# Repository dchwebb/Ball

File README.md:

# Ball

Overview
--------

Ball is a Bluetooth remote controller for a Eurorack modular synthesiser. The remote controller is a sphere containing a PCB with an STM32WB35 BLE transmitter connected to an STM MEMS gyroscope. The remote communicates over Bluetooth Low Energy (BLE) with a base unit. The base unit is a standard Eurorack module that converts the three axis gyroscope information into three control voltages.

Remote
------

The remote unit is designed around an STM32WB35 and powered from a Li-Po battery which is charged via a USB micro connection. Battery charging uses a MCP73831 Microchip Charge Management Controller. The battery can be isolated with a slide switch. A mosfet switches either the battery or USB power to a 2.8V linear regulator to power the MCU and gyroscope. A combined voltage divider passes the scaled battery voltage to an ADC in the MCU for battery level monitoring. The voltage divider also controls the inhibit line on the LDO to avoid drawing excessive power from the battery.

The 3-D sensing is carried out on an L3GD20 MEMS gyroscope from STM. This communicates with the MCU via full-duplex SPI. Initial prototyping was carried out using I2C on an Adafruit module and the pins for connecting to the module are fitted to the prototype board. The pins exposing the gyroscope ready and interrupt were bodged into the design via the (now unused) I2C pins. This allows waking from sleep mode via motion detection and readings to be taken from the gyroscope as soon as the ready interrupt fires.

The prototype Remote unit was fitted to a black sphere requisitioned from a child's toy.

[Schematic](https://raw.githubusercontent.com/dchwebb/Ball/main/ball_remote_schematic.pdf)

Base Unit
---------

The base unit also features an STM32WB35. This receives the 3 dimensional gyroscope data from the remote unit over BLE using the HID Joystick specification. (Theoretically this should mean the unit could also support other BLE game controllers but this has not been tested.)

The STM32WB does not contain any DACs so the gyroscope XYZ data is supplied as PWM data which is filtered and scaled to 0-5V. Three LEDs display the current level of each CV output. An additional blue LED showing BLE connection status is positioned behind a PCB Bluetooth 'window' - ie shines through the FR4 with no solder mask or copper.

[Schematic](https://raw.githubusercontent.com/dchwebb/Ball/main/ball_base_schematic.pdf)

Antennas and Matching Network
-----------------------------

The antenna matching network was designed using largely application notes and guesswork. The matching network consists of an 0402 PI network of capacitor/inductor/capacitor connected to an Ignion NN01_102 antenna. Whilst connection strength could probably be improved if matched with a VNA, communications work well in testing.

Power Management and Sleep
--------------------------

As the Remote unit is battery powered various systems are used to reduce power consumption:

When the unit is first powered or reset it begins fast advertising which allows for near-instant connections. After a configurable period has elapsed the unit switches to more infrequent advertising. After a further configurable period of inactivity the unit enters shutdown and can be restarted via the reset button.

Once a connection has been established to the base unit the remote will transmit at full speed (around 380Hz). If no motion is detected after a few seconds the unit will slow down the sampling rate to 190Hz and if no motion is detected after a few more seconds will enter sleep mode. The device can woken via motion (using the gyroscope's interrupt pin), or from the base unit (ie to request a battery level update). If woken from motion the sleep process will repeat once the unit is at rest, or if woken via RF will immediately return to sleep.

The Remote unit's USB peripheral is disabled unless a battery reading of 100% is registered (ie the unit is connected to USB and powered via VBUS). If USB is enabled current draw is around 2mA higher than usual. a USB serial command will also momentarily wake the unit if sleeping.

Measured current consumption of the remote (MCU and all other hardware) is measured as approximately:

- Advertising: 13mA
- Connected: 16mA
- Sleep: 10mA
- Shutdown: 0.4mA

USB Serial Console
------------------

Both the base and remote have USB serial consoles providing a range of diagnostic and configuration information:

Development Software
--------------------

- Schematic and PCB design done in Kicad v6/7.
- Firmware developed in STM32CubeIDE v1.13.2.

Errata
------

Remote:

- SPI MOSI and MISO connections swapped
- Gyroscope Interrupt and Ready pins bodged onto unused I2C pins
- Mosfet Q1 source and drain pins swapped
- Battery charging and monitoring circuit could be improved (eg using a dedicated Battery Management IC such as TI's BQ24079QWRGTRQ1)

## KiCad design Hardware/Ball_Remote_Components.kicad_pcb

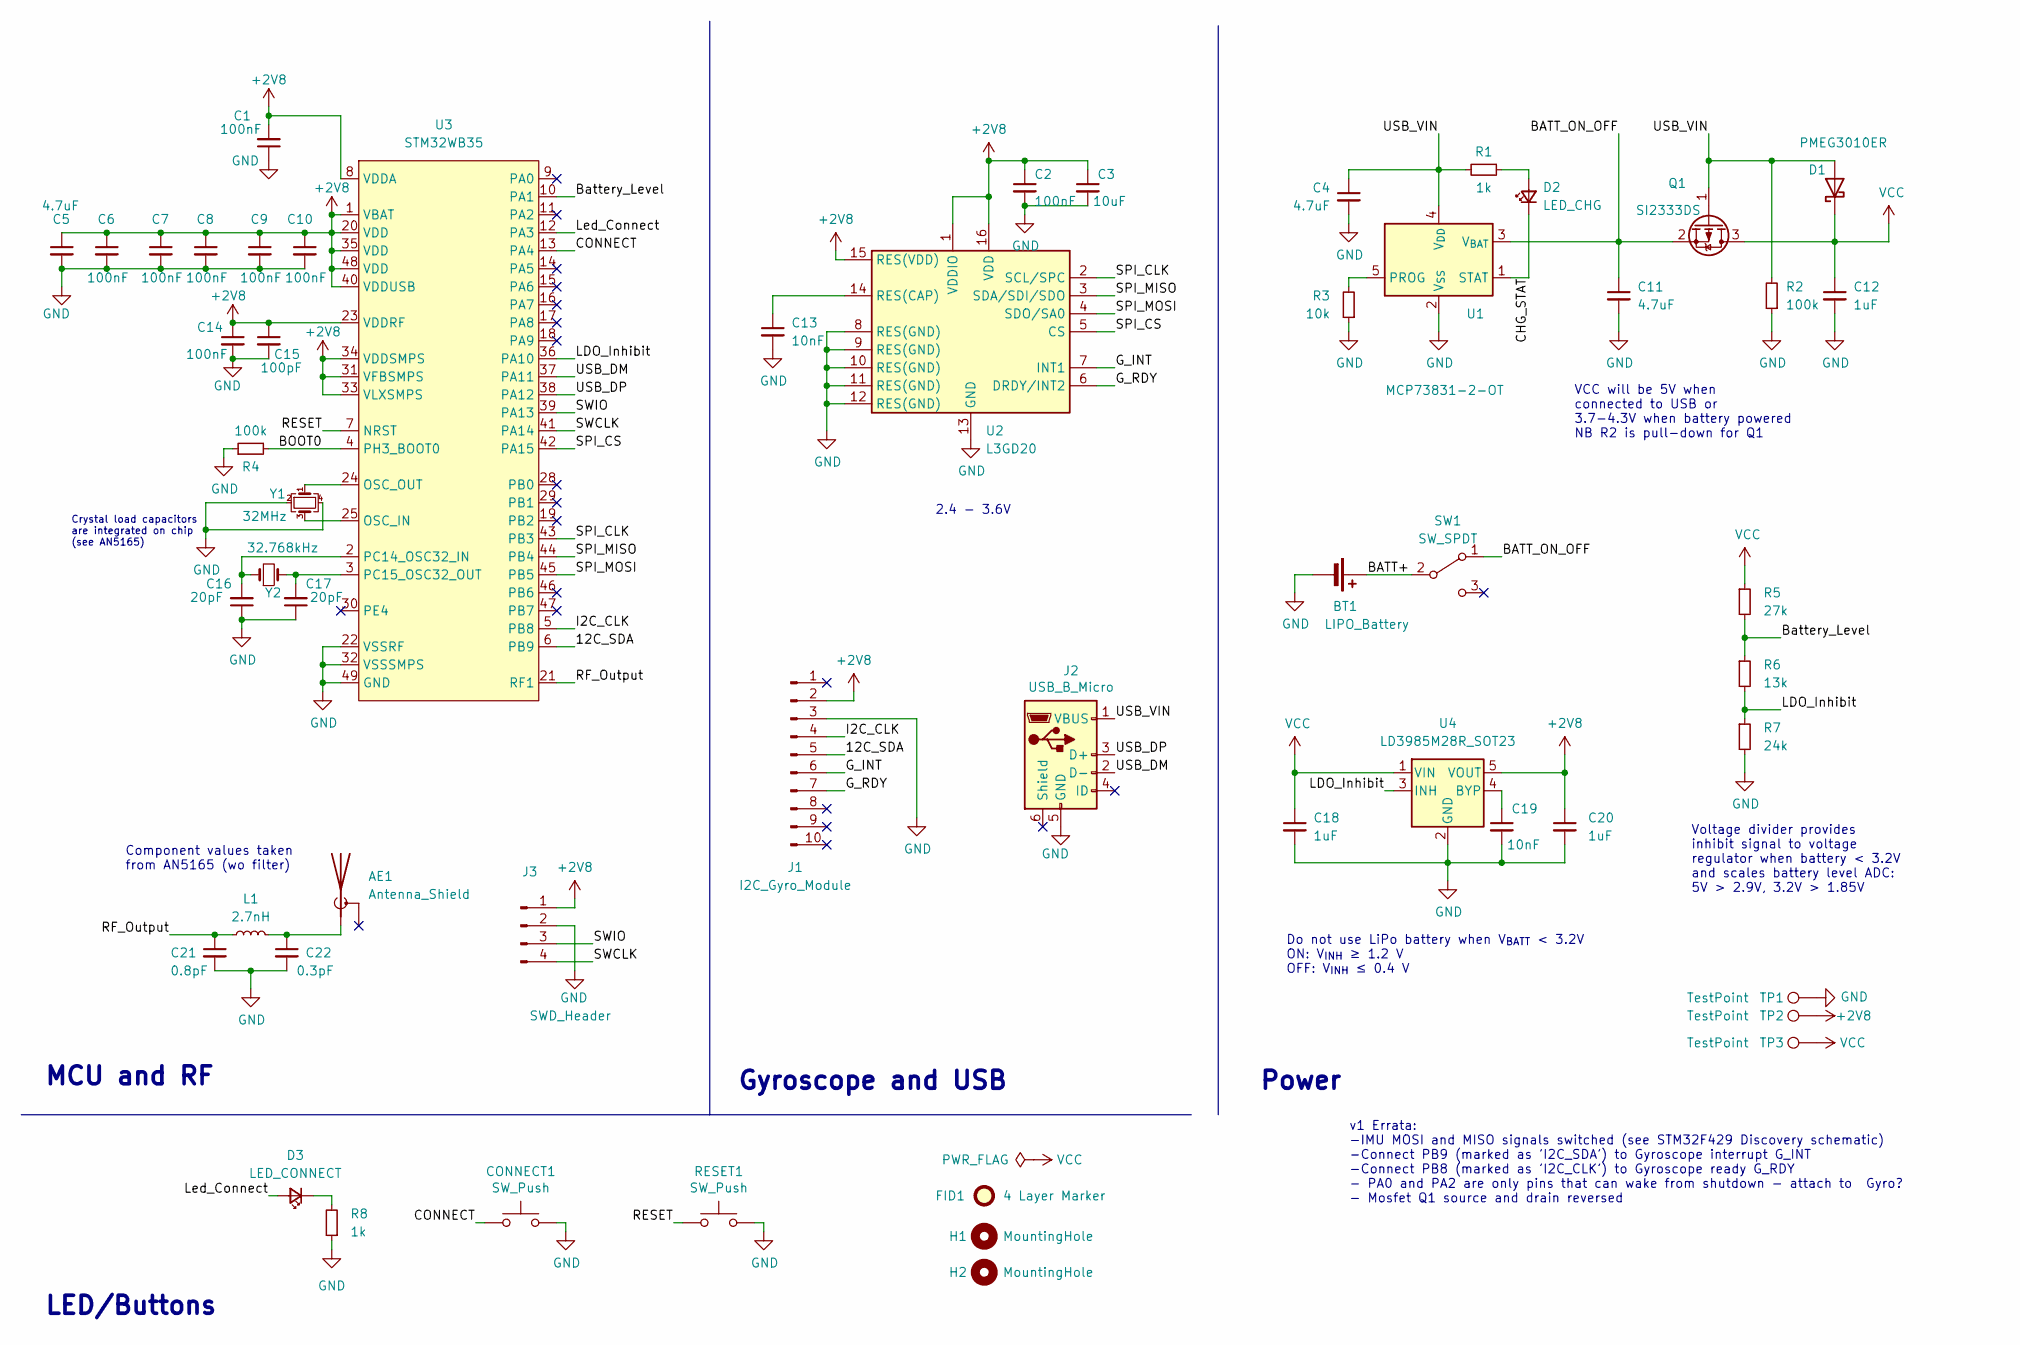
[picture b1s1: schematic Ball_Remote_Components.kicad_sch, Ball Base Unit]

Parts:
AE1: Antenna_Shield; NN01_102
BT1: LIPO_Battery; PinHeader_1x02_P2.54mm_Vertical
C1, C2, C6, C8, C9, C10, C14: 100nF; C_0603_1608Metric
C3: 10uF; C_0603_1608Metric
C4, C5, C11: 4.7uF; C_0603_1608Metric
C7: 100nF; C_0402_1005Metric
C12, C18, C20: 1uF; C_0603_1608Metric
C13, C19: 10nF; C_0603_1608Metric
C15: 100pF; C_0402_1005Metric
C16, C17: 20pF; C_0603_1608Metric
C21: 0.8pF; C_0402_1005Metric
C22: 0.3pF; C_0402_1005Metric
CONNECT1: SW_Push; SW_SPST_EVQQ2
D1: PMEG3010ER; D_SMA
D2: LED_CHG; LED_0603_1608Metric
D3: LED_CONNECT; LED_0603_1608Metric
FID1: 4 Layer Marker; 4_Layer_Markers
H1, H2: MountingHole; MountingHole_3.2mm_M3
J1: I2C_Gyro_Module; PinSocket_1x10_P2.54mm_Vertical
J2: USB_B_Micro; USB_Micro-B_Amphenol
J3: SWD_Header; SWD_header
L1: 2.7nH; L_0402_1005Metric
Q1: SI2333DS; SOT-23
R1: 1k; R_0603_1608Metric; Part_Number C25803
R2, R4: 100k; R_0603_1608Metric; Part_Number C25803
R3: 10k; R_0603_1608Metric; Part_Number C25803
R5: 27k; R_0603_1608Metric; Part_Number C25803
R6: 13k; R_0603_1608Metric; Part_Number C25803
R7: 24k; R_0603_1608Metric; Part_Number C25803
R8: 1k; R_0603_1608Metric
RESET1: SW_Push; SW_Tactile_SPST_Angled_PTS645Vx58-2LFS
SW1: SW_SPDT; SPDT_Slide_Switch
TP1, TP2, TP3: TestPoint; 1.3mm_Test_Point
U1: MCP73831-2-OT; SOT-23-5
U2: L3GD20; LGA-16_4x4mm_P0.65mm_LayoutBorder4x4y
U3: STM32WB35; QFN-48-1EP_7x7mm_P0.5mm_EP5.15x5.15mm_ThermalVias
U4: LD3985M28R_SOT23; SOT-23-5
Y1: 32MHz; Crystal_SMD_Abracon_ABM10-4Pin_2.5x2.0mm
Y2: 32.768kHz; Crystal_SMD_2012-2Pin_2.0x1.2mm

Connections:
+2V8: C1.2, C2.1, C3.1, C5.1, C6.1, C7.1, C8.1, C9.1, C10.1, C14.1, C15.1, C20.1, J1.2, J3.1, TP2.1, U2.1 (VDDIO), U2.15 (RES(VDD)), U2.16 (VDD), U3.1 (VBAT), U3.8 (VDDA), U3.20 (VDD), U3.23 (VDDRF), U3.31 (VFBSMPS), U3.33 (VLXSMPS), U3.34 (VDDSMPS), U3.35 (VDD), U3.40 (VDDUSB), U3.48 (VDD), U4.5 (VOUT)
/12C_SDA: J1.5, U3.6 (PB9)
/BATT+: BT1.1 (+), SW1.2 (B)
/BATT_ON_OFF: C11.1, Q1.2 (S), SW1.1 (A), U1.3 (V_{BAT})
/BOOT0: R4.2, U3.4 (PH3_BOOT0)
/Battery_Level: R5.2, R6.1, U3.10 (PA1)
/CHG_STAT: D2.1 (K), U1.1 (STAT)
/CONNECT: CONNECT1.1, U3.13 (PA4)
/G_INT: J1.6, U2.7 (INT1)
/G_RDY: J1.7, U2.6 (DRDY/INT2)
/I2C_CLK: J1.4, U3.5 (PB8)
/LDO_Inhibit: R6.2, R7.1, U3.36 (PA10), U4.3 (INH)
/Led_Connect: D3.2 (A), U3.12 (PA3)
/RESET: RESET1.1, U3.7 (NRST)
/RF_Output: C21.1, L1.1, U3.21 (RF1)
/SPI_CLK: U2.2 (SCL/SPC), U3.43 (PB3)
/SPI_CS: U2.5 (CS), U3.42 (PA15)
/SPI_MISO: U2.3 (SDA/SDI/SDO), U3.44 (PB4)
/SPI_MOSI: U2.4 (SDO/SA0), U3.45 (PB5)
/SWCLK: J3.4, U3.41 (PA14)
/SWIO: J3.3, U3.39 (PA13)
/USB_DM: J2.2 (D-), U3.37 (PA11)
/USB_DP: J2.3 (D+), U3.38 (PA12)
/USB_VIN: C4.1, D1.2 (A), J2.1 (VBUS), Q1.1 (G), R1.2, R2.2, U1.4 (V_{DD})
GND: BT1.2 (-), C1.1, C2.2, C3.2, C4.2, C5.2, C6.2, C7.2, C8.2, C9.2, C10.2, C11.2, C12.2, C13.2, C14.2, C15.2, C16.1, C17.1, C18.2, C19.2, C20.2, C21.2, C22.2, CONNECT1.2, J1.3, J2.5 (GND), J3.2, R2.1, R3.1, R4.1, R7.2, R8.1, RESET1.2, TP1.1, U1.2 (V_{SS}), U2.8 (RES(GND)), U2.9 (RES(GND)), U2.10 (RES(GND)), U2.11 (RES(GND)), U2.12 (RES(GND)), U2.13 (GND), U3.22 (VSSRF), U3.32 (VSSSMPS), U3.49 (GND), U4.2 (GND), Y1.2, Y1.4
unnamed: AE1.1 (A), C22.1, L1.2
unnamed: D2.2 (A), R1.1
unnamed: D3.1 (K), R8.2
unnamed: R3.2, U1.5 (PROG)
unnamed: C13.1, U2.14 (RES(CAP))
unnamed: U3.25 (OSC_IN), Y1.3
unnamed: U3.24 (OSC_OUT), Y1.1
unnamed: C16.2, U3.2 (PC14_OSC32_IN), Y2.1
unnamed: C17.2, U3.3 (PC15_OSC32_OUT), Y2.2
unnamed: C19.1, U4.4 (BYP)
VCC: C12.1, C18.1, D1.1 (K), Q1.3 (D), R5.1, TP3.1, U4.1 (VIN)

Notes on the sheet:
MCU and RF
Do not use LiPo battery when V_{BATT} < 3.2V ON: V_{INH} ≥ 1.2 V OFF: V_{INH} ≤ 0.4 V
Power
Gyroscope and USB
Component values taken from AN5165 (wo filter)
Voltage divider provides inhibit signal to voltage regulator when battery < 3.2V and scales battery level ADC: 5V > 2.9V, 3.2V > 1.85V
2.4 - 3.6V
LED/Buttons
VCC will be 5V when connected to USB or 3.7-4.3V when battery powered NB R2 is pull-down for Q1
v1 Errata: -IMU MOSI and MISO signals switched (see STM32F429 Discovery schematic) -Connect PB9 (marked as 'I2C_SDA') to Gyroscope interrupt G_INT -Connect PB8 (marked as 'I2C_CLK') to Gyroscope ready G_RDY - PA0 and PA2 are only pins that can wake from shutdown - attach to Gyro? - Mosfet Q1 source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
Crystal load capacitors are integrated on chip (see AN5165)

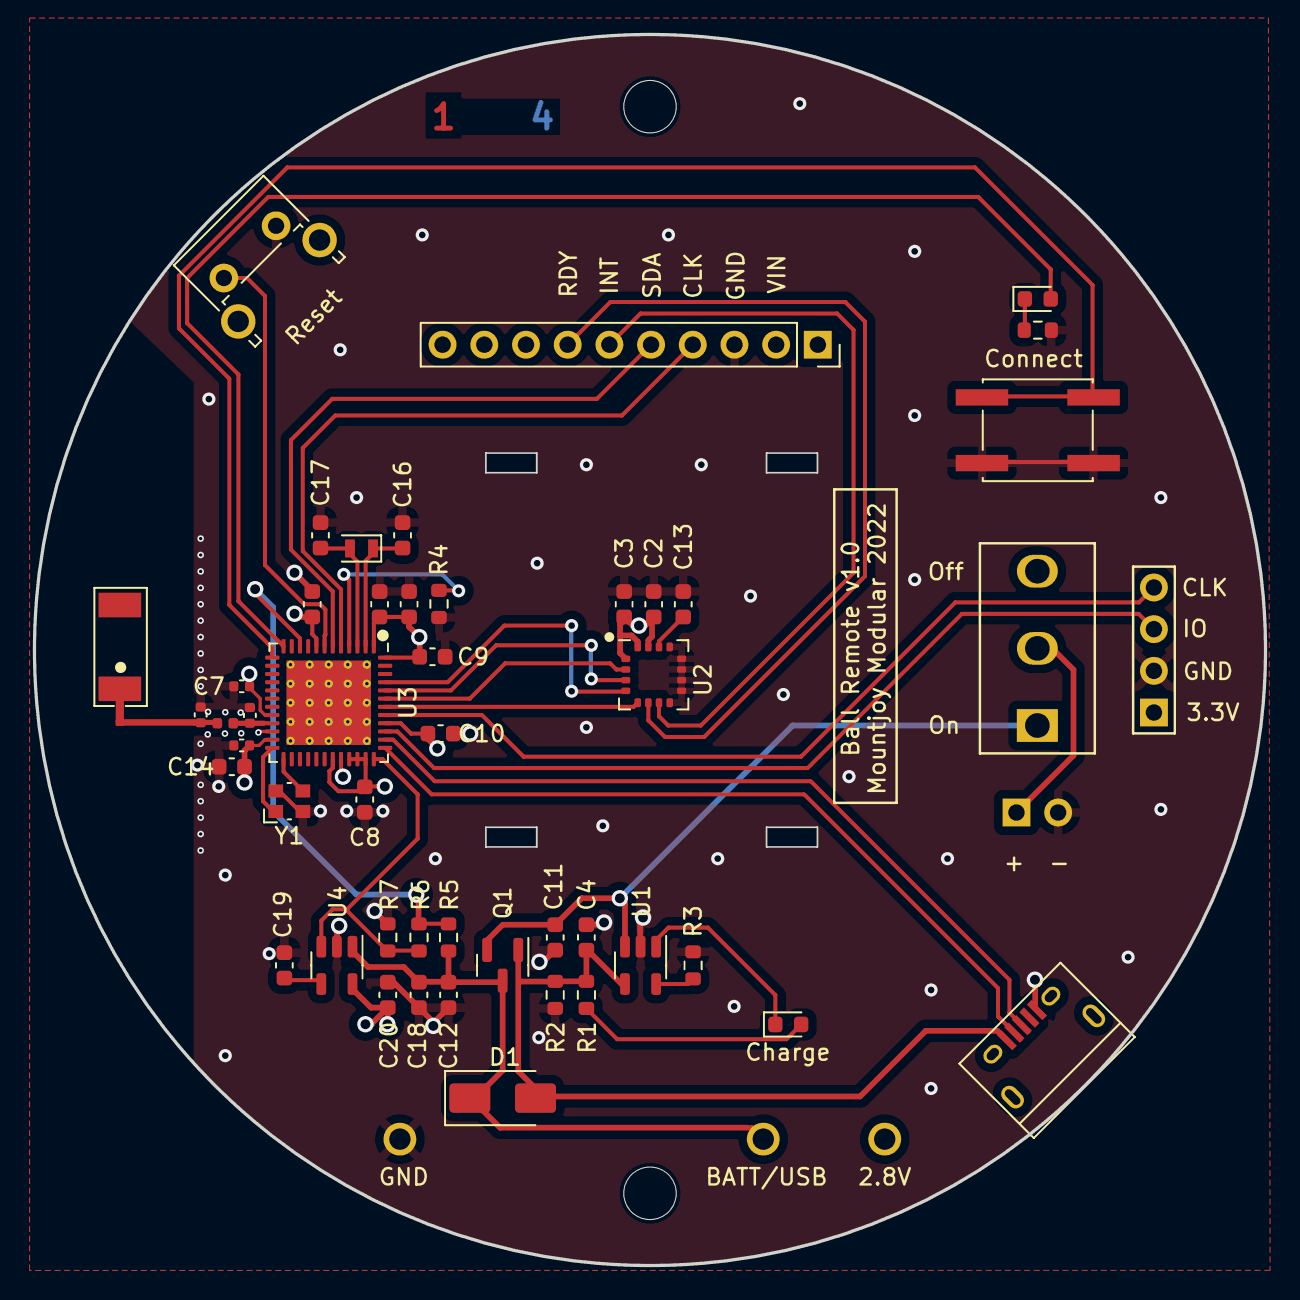
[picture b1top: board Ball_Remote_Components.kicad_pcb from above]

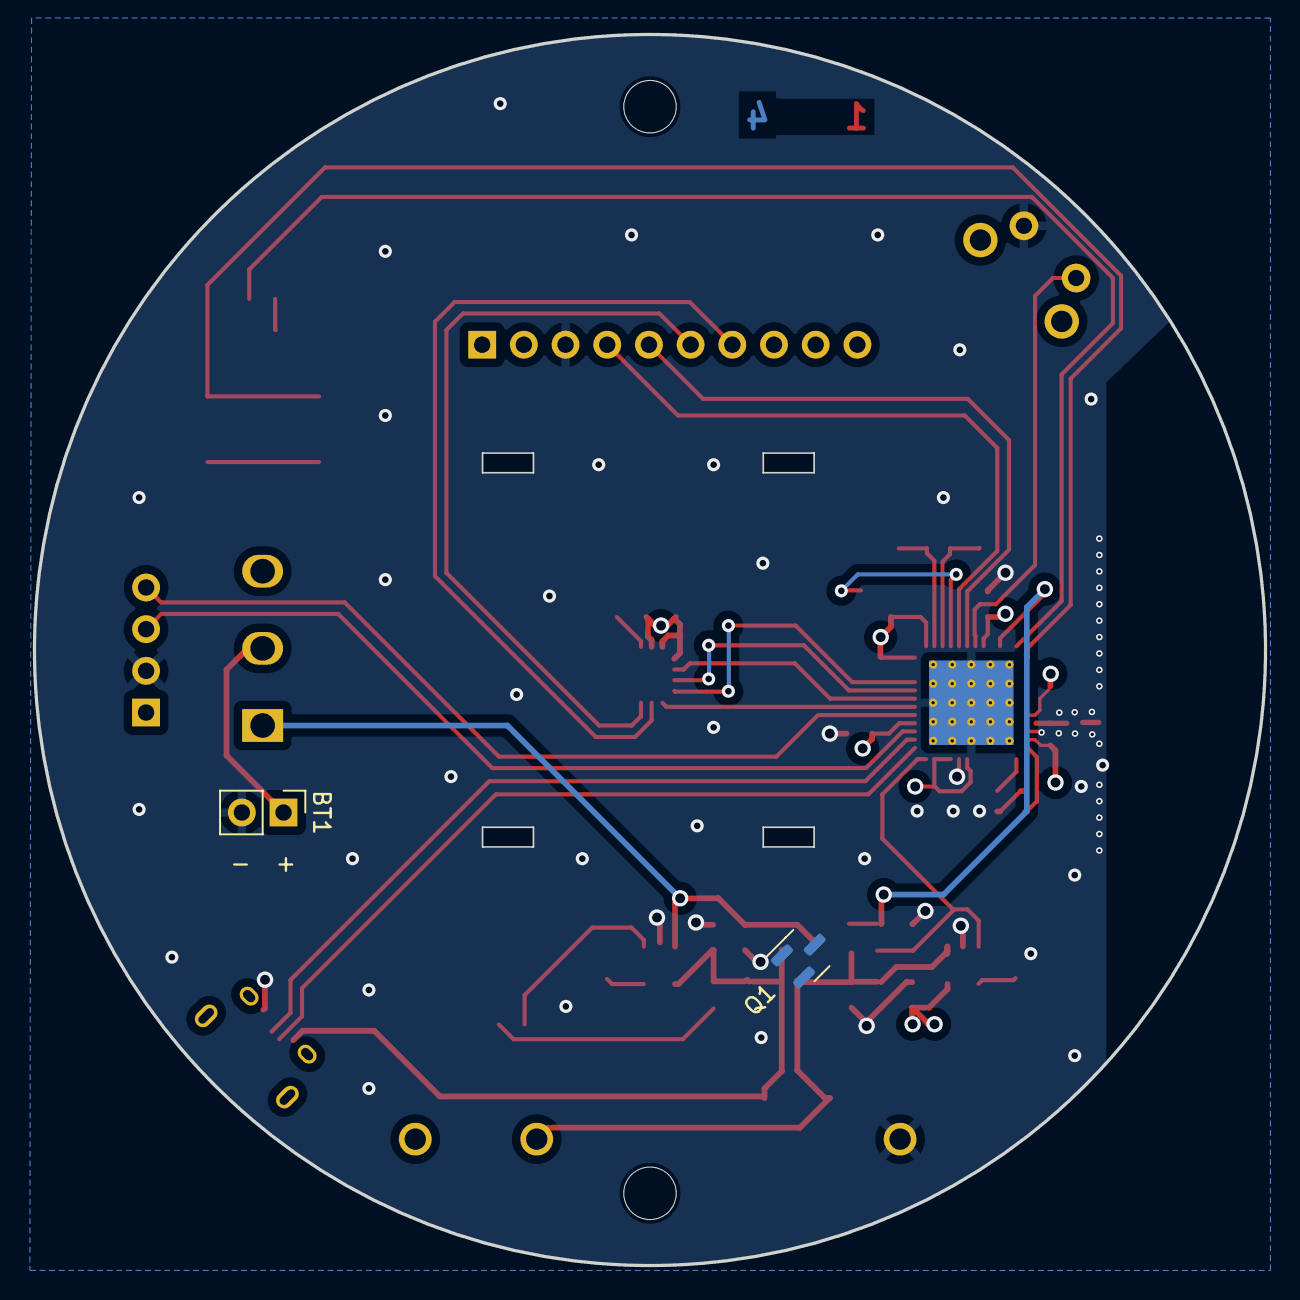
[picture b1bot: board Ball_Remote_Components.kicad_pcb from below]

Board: 4 copper layers, 75.0 x 75.0 mm, 56 parts (2 on the bottom side), 36 nets.

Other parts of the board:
Q1#2: SI2333DS; SOT-23

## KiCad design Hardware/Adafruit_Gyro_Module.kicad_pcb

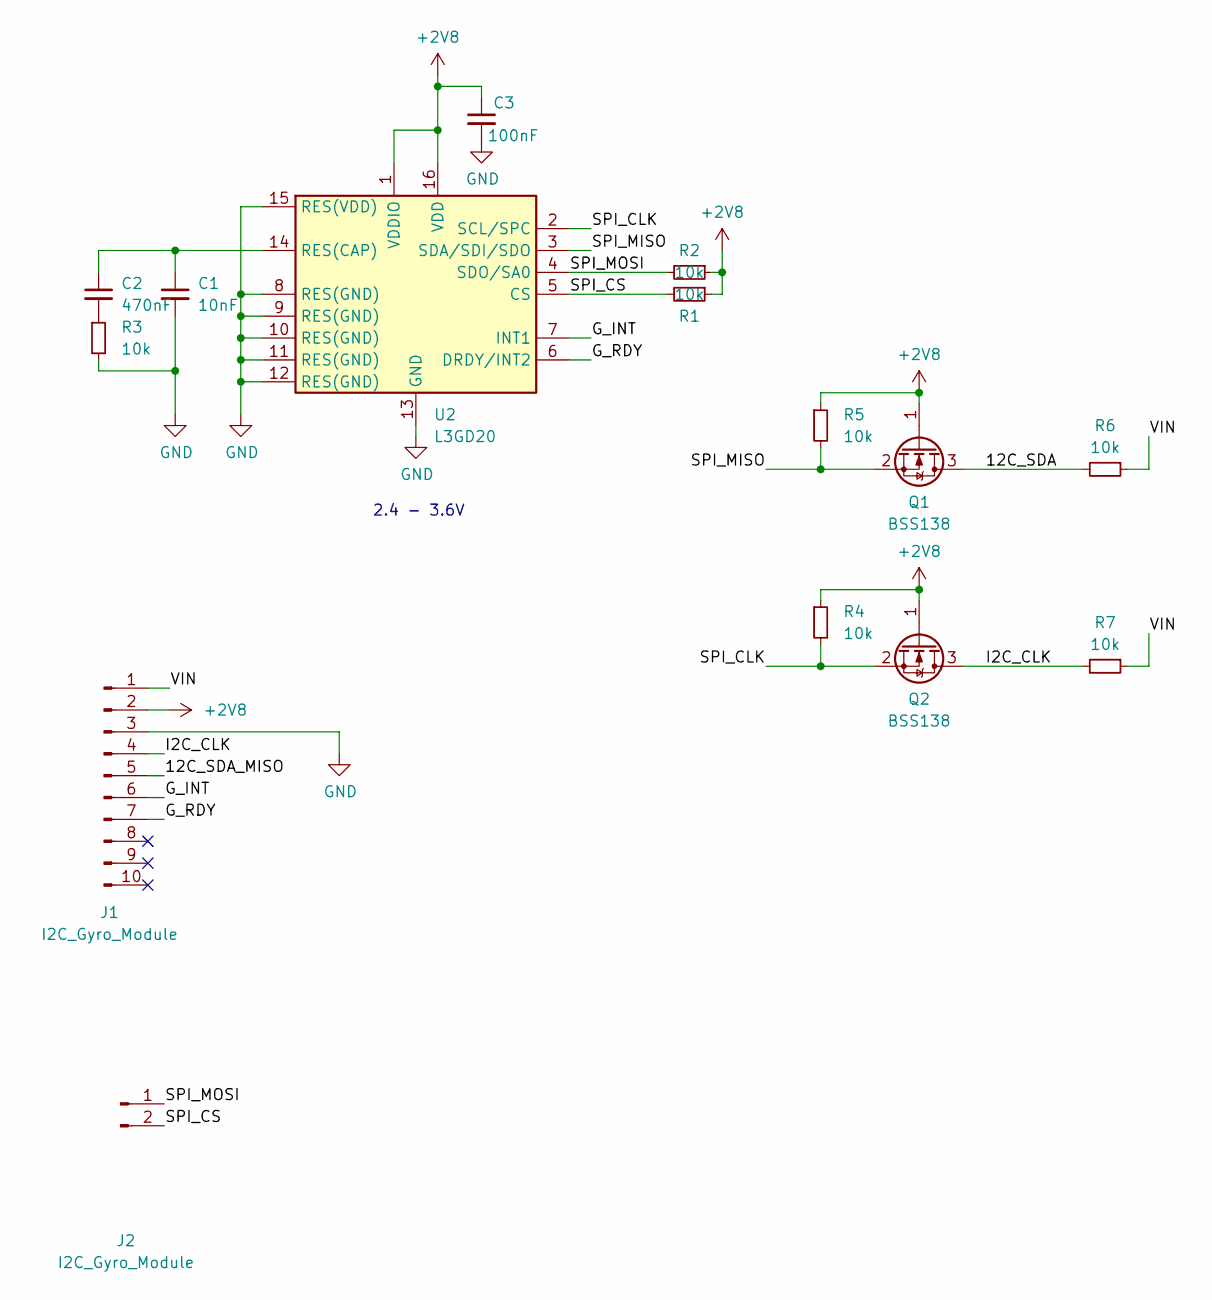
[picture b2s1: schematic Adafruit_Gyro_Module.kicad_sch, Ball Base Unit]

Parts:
C1: 10nF; C_0603_1608Metric
C2: 470nF; C_0603_1608Metric
C3: 100nF; C_0603_1608Metric
J1: I2C_Gyro_Module; PinSocket_1x10_P2.54mm_Vertical
J2: I2C_Gyro_Module; PinSocket_1x02_P2.54mm_Vertical
Q1, Q2: BSS138; SOT-23
R1, R2, R3, R4, R5, R6, R7: 10k; R_0603_1608Metric; Part_Number C25803
U2: L3GD20; LGA-16_4x4mm_P0.65mm_LayoutBorder4x4y

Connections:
+2V8: C3.1, J1.2, Q1.1 (G), Q2.1 (G), R1.1, R2.1, R4.1, R5.1, U2.1 (VDDIO), U2.16 (VDD)
/12C_SDA: Q1.3 (D), R6.2
/12C_SDA_MISO: J1.5
/G_INT: J1.6, U2.7 (INT1)
/G_RDY: J1.7, U2.6 (DRDY/INT2)
/I2C_CLK: J1.4, Q2.3 (D), R7.2
/SPI_CLK: Q2.2 (S), R4.2, U2.2 (SCL/SPC)
/SPI_CS: J2.2, R1.2, U2.5 (CS)
/SPI_MISO: Q1.2 (S), R5.2, U2.3 (SDA/SDI/SDO)
/SPI_MOSI: J2.1, R2.2, U2.4 (SDO/SA0)
/VIN: J1.1, R6.1, R7.1
GND: C1.2, C3.2, J1.3, R3.2, U2.8 (RES(GND)), U2.9 (RES(GND)), U2.10 (RES(GND)), U2.11 (RES(GND)), U2.12 (RES(GND)), U2.13 (GND), U2.15 (RES(VDD))
unnamed: C2.2, R3.1
unnamed: C1.1, C2.1, U2.14 (RES(CAP))

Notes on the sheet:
2.4 - 3.6V

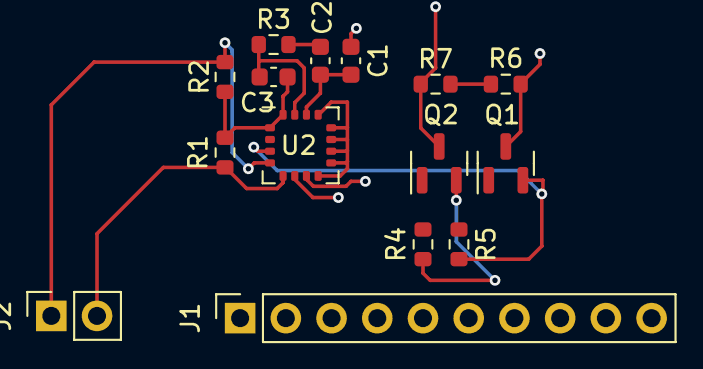
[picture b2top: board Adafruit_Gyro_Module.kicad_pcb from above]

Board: 2 copper layers, 15 parts (0 on the bottom side), 13 nets.

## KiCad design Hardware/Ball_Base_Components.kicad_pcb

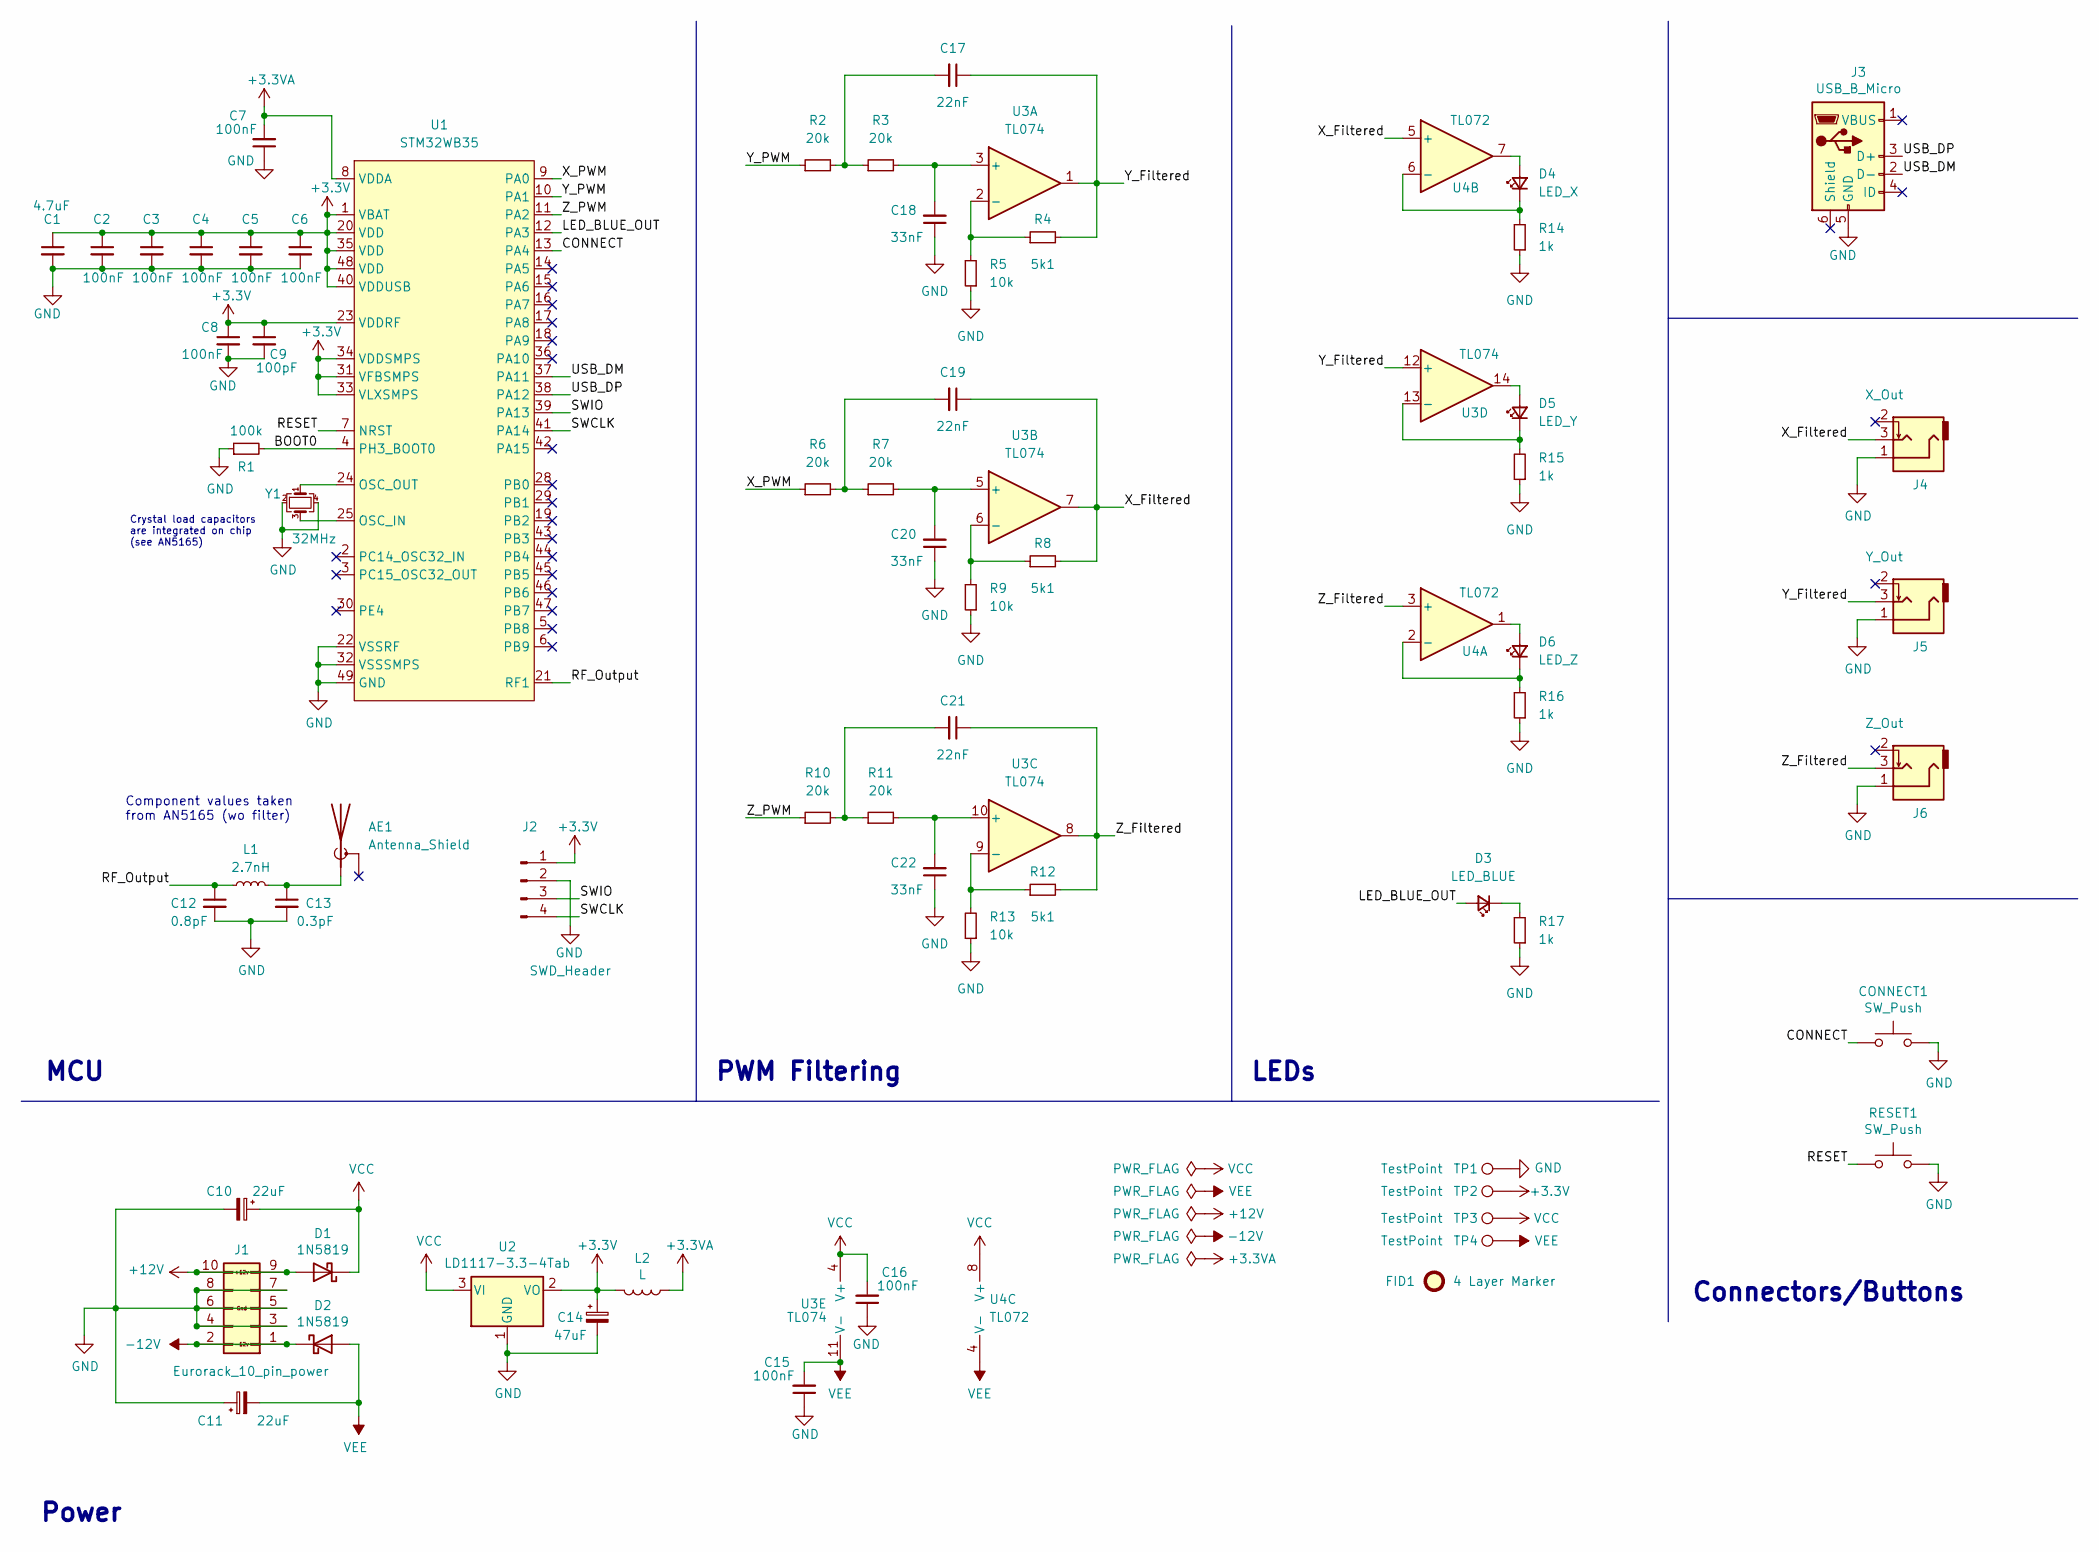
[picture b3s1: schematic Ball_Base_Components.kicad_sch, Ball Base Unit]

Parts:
AE1: Antenna_Shield; NN01_102
C1: 4.7uF; C_0603_1608Metric
C2, C4, C5, C6, C7, C8, C15, C16: 100nF; C_0603_1608Metric
C3: 100nF; C_0402_1005Metric
C9: 100pF; C_0402_1005Metric
C10: 22uF; CP_Elec_4x5.4; Part_Number C134798
C11: 22uF; CP_Elec_4x5.4; Part_Number C134793
C12: 0.8pF; C_0402_1005Metric
C13: 0.3pF; C_0402_1005Metric
C14: 47uF; CP_Elec_5x5.8; Part_Number C134798
C17, C19, C21: 22nF; C_0603_1608Metric
C18, C20, C22: 33nF; C_0603_1608Metric
CONNECT1: SW_Push; SW_Tactile_SPST_Angled_PTS645Vx58-2LFS
D1, D2: 1N5819; D_SOD-123; Part_Number C8598
D3: LED_BLUE; LED_D3.0mm_FlatTop
D4: LED_X; LED_D3.0mm_FlatTop
D5: LED_Y; LED_D3.0mm_FlatTop
D6: LED_Z; LED_D3.0mm_FlatTop
FID1: 4 Layer Marker; 4_Layer_Markers
J1: Eurorack_10_pin_power; Eurorack_10_pin_header
J2: SWD_Header; SWD_header
J3: USB_B_Micro; USB_Micro-B_Amphenol
J4: X_Out; Jack_3.5mm_QingPu_WQP-PJ302M_Horizontal
J5: Y_Out; Jack_3.5mm_QingPu_WQP-PJ302M_Horizontal
J6: Z_Out; Jack_3.5mm_QingPu_WQP-PJ302M_Horizontal
L1: 2.7nH; L_0402_1005Metric
L2: L; L_0805_2012Metric; Part_Number C1046
R1: 100k; R_0603_1608Metric; Part_Number C25803
R2, R3, R6, R7, R10, R11: 20k; R_0603_1608Metric
R4, R8, R12: 5k1; R_0603_1608Metric
R5, R9, R13: 10k; R_0603_1608Metric
R14, R15, R16, R17: 1k; R_0603_1608Metric
RESET1: SW_Push; SW_Tactile_SPST_Angled_PTS645Vx58-2LFS
TP1, TP2, TP3, TP4: TestPoint; 1.3mm_Test_Point
U1: STM32WB35; QFN-48-1EP_7x7mm_P0.5mm_EP5.15x5.15mm_ThermalVias
U2: LD1117-3.3-4Tab; SOT-223-3_TabPin2
U3: TL074; SOIC-14_3.9x8.7mm_P1.27mm
U4: TL072; SOIC-8_3.9x4.9mm_P1.27mm
Y1: 32MHz; Crystal_SMD_Abracon_ABM10-4Pin_2.5x2.0mm

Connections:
+3.3VA: C7.2, L2.1, U1.8 (VDDA)
+3V3: C1.1, C2.1, C3.1, C4.1, C5.1, C6.1, C8.1, C9.1, C14.1, J2.1, L2.2, TP2.1, U1.1 (VBAT), U1.20 (VDD), U1.23 (VDDRF), U1.31 (VFBSMPS), U1.33 (VLXSMPS), U1.34 (VDDSMPS), U1.35 (VDD), U1.40 (VDDUSB), U1.48 (VDD), U2.2 (VO)
+12V: D1.2 (A), J1.9, J1.10
-12V: D2.1 (K), J1.1, J1.2
/BOOT0: R1.2, U1.4 (PH3_BOOT0)
/CONNECT: CONNECT1.1, U1.13 (PA4)
/LED_BLUE_OUT: D3.2 (A), U1.12 (PA3)
/RESET: RESET1.1, U1.7 (NRST)
/RF_Output: C12.1, L1.1, U1.21 (RF1)
/SWCLK: J2.4, U1.41 (PA14)
/SWIO: J2.3, U1.39 (PA13)
/USB_DM: J3.2 (D-), U1.37 (PA11)
/USB_DP: J3.3 (D+), U1.38 (PA12)
/X_Filtered: C19.1, J4.3, R8.2, U3.7, U4.5 (+)
/X_PWM: R6.1, U1.9 (PA0)
/Y_Filtered: C17.1, J5.3, R4.2, U3.1, U3.12 (+)
/Y_PWM: R2.1, U1.10 (PA1)
/Z_Filtered: C21.1, J6.3, R12.2, U3.8, U4.3 (+)
/Z_PWM: R10.1, U1.11 (PA2)
GND: C1.2, C2.2, C3.2, C4.2, C5.2, C6.2, C7.1, C8.2, C9.2, C10.2, C11.1, C12.2, C13.2, C14.2, C15.1, C16.1, C18.1, C20.1, C22.1, CONNECT1.2, J1.3, J1.4, J1.5, J1.6, J1.7, J1.8, J2.2, J3.5 (GND), J4.1, J5.1, J6.1, R1.1, R5.1, R9.1, R13.1, R14.1, R15.1, R16.1, R17.1, RESET1.2, TP1.1, U1.22 (VSSRF), U1.32 (VSSSMPS), U1.49 (GND), U2.1 (GND), Y1.2, Y1.4
unnamed: AE1.1 (A), C13.1, L1.2
unnamed: C17.2, R2.2, R3.1
unnamed: C18.2, R3.2, U3.3 (+)
unnamed: C19.2, R6.2, R7.1
unnamed: C20.2, R7.2, U3.5 (+)
unnamed: C21.2, R10.2, R11.1
unnamed: C22.2, R11.2, U3.10 (+)
unnamed: D3.1 (K), R17.2
unnamed: D4.1 (K), R14.2, U4.6 (-)
unnamed: D4.2 (A), U4.7
unnamed: D5.1 (K), R15.2, U3.13 (-)
unnamed: D5.2 (A), U3.14
unnamed: D6.1 (K), R16.2, U4.2 (-)
unnamed: D6.2 (A), U4.1
unnamed: R4.1, R5.2, U3.2 (-)
unnamed: R8.1, R9.2, U3.6 (-)
unnamed: R12.1, R13.2, U3.9 (-)
unnamed: U1.24 (OSC_OUT), Y1.1
unnamed: U1.25 (OSC_IN), Y1.3
VCC: C10.1, C16.2, D1.1 (K), TP3.1, U2.3 (VI), U3.4 (V+), U4.8 (V+)
VEE: C11.2, C15.2, D2.2 (A), TP4.1, U3.11 (V-), U4.4 (V-)

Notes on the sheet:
LEDs
MCU
Power
PWM Filtering
Component values taken from AN5165 (wo filter)
Connectors/Buttons
Crystal load capacitors are integrated on chip (see AN5165)

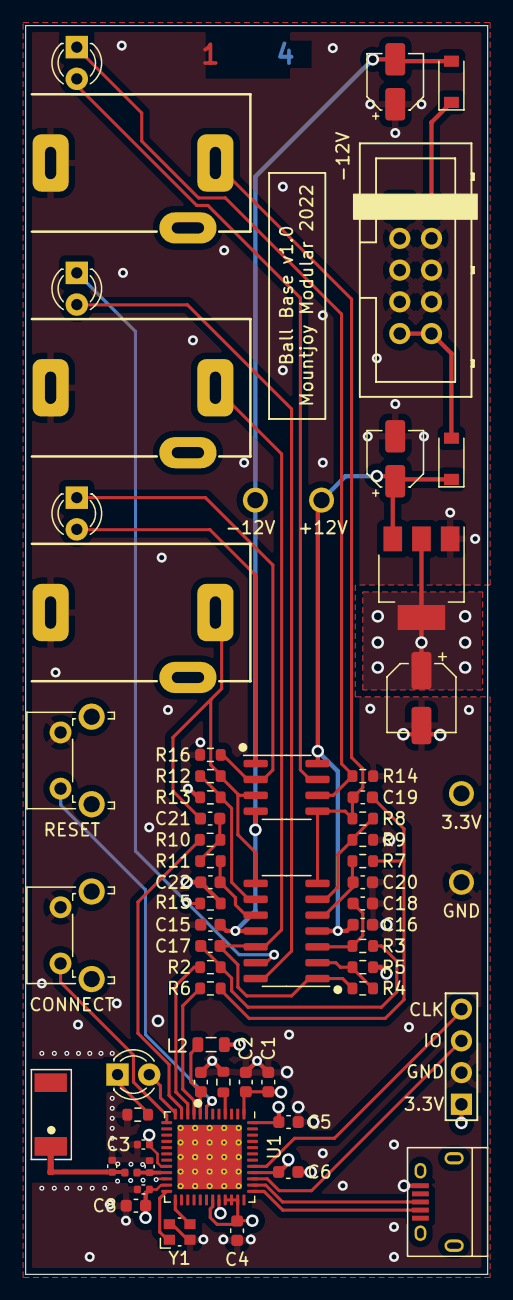
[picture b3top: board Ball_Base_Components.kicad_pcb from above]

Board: 4 copper layers, 37.0 x 100.0 mm, 66 parts (0 on the bottom side), 41 nets.

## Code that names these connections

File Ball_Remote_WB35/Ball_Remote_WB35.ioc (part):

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Mcu.Name=STM32WB35C(C-E)UxA
Mcu.Package=UFQFPN48
Mcu.UserName=STM32WB35CEUxA
PA1.Signal=ADCx_IN6
PA11.Mode=Device
PA11.Signal=USB_DM
PA12.Mode=Device
PA12.Signal=USB_DP
PA15.Mode=NSS_Signal_Hard_Input
PA15.Signal=SPI1_NSS
PB3.Mode=Full_Duplex_Master
PB3.Signal=SPI1_SCK
PB4.Mode=Full_Duplex_Master
PB4.Signal=SPI1_MISO
PB5.Mode=Full_Duplex_Master
PB5.Signal=SPI1_MOSI
PB8.Mode=I2C
PB8.Signal=I2C1_SCL
PB9.Mode=I2C
PB9.Signal=I2C1_SDA
PC14-OSC32_IN.Mode=LSE-External-Oscillator
PC14-OSC32_IN.Signal=RCC_OSC32_IN
PC15-OSC32_OUT.Mode=LSE-External-Oscillator
PC15-OSC32_OUT.Signal=RCC_OSC32_OUT
RCC.HSE_VALUE=32000000
RCC.SYSCLKFreq_VALUE=32000000
RCC.SYSCLKSource=RCC_SYSCLKSOURCE_PLLCLK
board=custom

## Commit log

2021-11-23 Started converting to C++
2021-11-24 Clean up and convert more files to C++
2021-11-25 Major code reorganisations; started removing HAL library dependencies
2021-11-25 Rewrite of initial hardware and clock configuration
2021-11-26 Directly initialise IPCC peripheral; cleaned up interrupt handers
2021-11-26 Converted RTC initialisation from HAL; fixed some clock issues when cold starting
2021-11-26 Further code clean up
2021-11-27 Converted GPIO initialisation from HAL
2021-11-27 Removed HAL dependencies for UART; UART receive working
2021-11-28 Refactor P2P references to HID; added disconnect task
2021-11-28 Added additional PWM channel
2021-11-29 Added Remote firmware project
2021-11-29 Work on startup routine
2021-11-29 Cleaned up App_entry and mainly finished converting HAL startup
2021-11-29 Converted interrupts and GPIO initialisation
2021-11-30 Started cleaning up HID server application
2021-11-30 Started converting HID server to use Joystick report
2021-12-01 Rewrite of BAS application; tested under Windows and notifications working
2021-12-03 Started implementing I2C for ST LSM303 magnetometer
2021-12-04 Implemented basic method to read magnetometer headings via I2C
2021-12-05 I2C DMA basic functionality working
2021-12-06 Decoded I2c compass data; implemented continuous capture at ~1kHz
2021-12-07 Cleaned up app_ble.cpp
2021-12-08 More clean up of app_ble
2021-12-09 Updated base unit to support 3 channels of HID to PWM
2021-12-16 Started implementing usb
2021-12-20 Fixed issues caused by incorrect PMA address in ST headers
2021-12-21 Integrated serial handler to process usb CDC commands; basic tests using in conjunction with BLE
2021-12-23 Updates to use usb for printf; Start implementing diagnostic device discovery
2021-12-23 More work on discovery info output
2021-12-27 Attempts to get advertising data printing reliably
2021-12-27 More attempts to work around print issues
2022-01-03 Started converting App Ble to C++ class
2022-01-04 More class conversion
2022-01-05 More class tidying
2022-01-06 Class conversion and code clean-up
2022-01-08 Added mechanism to return HID report map
2022-01-12 Starting to get base connecting to remote using both STMWB55s
2022-01-13 Converting remote HID to classes
2022-01-13 Hid device controller converted to C++ class
2022-01-15 Refactoring; convert ble_app to C++ class
2022-01-18 Refactoring; experiments with workarounds for fus/coprocessor update breaking usb
2022-01-18 Code folders reorganisation
2022-01-21 Started work on low power mode
2022-01-23 More work on low power modes
2022-01-24 Sleep mode working fairly well
2022-01-25 Started simplifying service control callback structure
2022-01-26 Implemented shutdown and reboot mode; more work on sleep mechanism
    refactoring of service control, making hids, bas and dis consistent classes
2022-01-28 Added various i2c debug commands; started looking at support for ST L3GD20 gyroscope
2022-02-06 Started implementing control mechanism with calibration and offset handling
2022-02-07 Updated clock from 32MHz to 64MHz
2022-02-08 Added console info function to view current settings; Minor tweaks
2022-02-08 Testing removing RTC functionality from Base unit
2022-02-10 Calibration updates; I2C Handling improvements; Started Base Schematic
2022-02-14 Rough Ball Base PCB layout
2022-02-17 First draft of Ball Base pcb completed
2022-02-18 Base PCB Updates and resize
2022-02-19 Base - started panel PCB
2022-02-23 Minor PCB Updates
2022-02-23 More PCB Clean up
2022-02-24 PCB Updates
2022-02-27 Started layout of Ball Remote schematic
2022-03-05 Work on remote PCB
2022-03-13 Remote schematic and PCB clean up
2022-03-14 More PCB clean-up
2022-03-22 Preparation of Gerbers for manufacturing
2022-03-22 Updated panel to reduce copper pour and solder mask
2022-03-23 Fixed 4-layer marker incorrect copper layers
2022-06-21 Created test firmware for STM32WB35 hardware (not yet working)
2022-06-25 Testing with prototype remote hardware; implemented battery level monitor
2022-06-28 Added Provisional Gyroscope SPI code
2022-06-28 Added first draft readme
2023-08-29 Preparing to test Remote board
2023-09-03 Updating Gyroscope code to use SPI
    Basic communication with Gyro SPI working; DMA not yet implemented
2023-09-04 Switched SPI to use software CS
2023-09-04 First attempt at optimising multiple SPI reads
2023-09-05 Cleaned up gyro code
2023-09-05 Updated production code to support Gyro SPI
    Started updating USB code; basic timer notification working
2023-09-06 Added Battery Voltage output to BAS service
    Fixed RSSI output
    Fixed bug sequencing gyro SPI reads
2023-09-06 Handle wireless stack not running
2023-09-06 Battery level checked periodically and updated if required
2023-09-07 Updated USB to use class handlers
2023-09-07 Cleaned up USB and BAS service
2023-09-07 Joystick and Battery Notifications triggered by sequencer to avoid lockups
2023-09-08 Updated ST library files
2023-09-08 Updated notification task type to attempt to resolve crashes
2023-09-08 More library files updated
2023-09-08 Disabled HSEM interrupt as apparently not used
2023-09-08 Removed redundant HAL and library files
2023-09-08 Updated USB PMA handling
2023-09-09 Cleaned up schematic to fix issues in Kicad 7; refactored USBClass to USBMain
2023-09-09 Cleaned up app_conf.h and transferred many settings to app_ble.h
2023-09-10 More clean up of app_ble initialisation
2023-09-11 Starting to update Base firmware
2023-09-12 Created test project to verify Base radio functionality with Remote firmware (working fine)
2023-09-13 Updated library files and fixed connection issue
2023-09-13 Updated USB class
2023-09-13 Cleaning initialisation and interrupts
2023-09-13 Cleaning out unused library files
2023-09-13 Refactoring app_ble class
2023-09-13 Clean up of header and configuration files
2023-09-13 Fixed CDC hidmap function
2023-09-14 Added sprintf wrapper function to CDC
2023-09-14 Minor changes
2023-09-18 Fixes to USB CDC corruptions and missing data
2023-09-18 Cleaned up connection code; added battery level request
2023-09-19 Cleaned up HID state machine
2023-09-19 Auto calibrate on startup
    Cleaned up status output
2023-09-19 Started implementing dynamic offset adjustment
2023-09-20 More work on calibration
2023-09-21 Connection LED flashes during connection process
2023-09-21 Started adding config saving
2023-09-22 Calibrated offsets stored to Flash
2023-09-22 Updated remote usb to fix transmission glitches
2023-09-24 Tweaks to gyro settings
2023-09-24 Added mechanism to read and write gyroscope registers over BLE from Base
2023-09-25 Updates to mechanism to read/write gyro registers from base
    Not fully working - when reading notification not always received
2023-09-25 Clean up handle variable names
2023-09-26 More tweaks to gyro register reading/writing
    Still not working properly
2023-09-26 Project clean up; split gyro register into command and data
2023-09-26 Gyro register reading/writing from base working
    Though hacky - has to periodically read to get values as notifications getting lost
2023-09-26 Adding retry logic simplified gyro read
2023-09-26 Minor code clean up
2023-09-26 Cleaned up printf output
2023-09-28 Removed old projects; 'Connect' button now controls sleep state
2023-09-28 Disable and re-enable USB when sleeping
2023-09-29 Added mechanism to Remote to detect no movement for pausing output
2023-09-30 Track no movement duration in gyroscope
2023-09-30 Sleep mode on remote with wake-up from gyro interrupt working
    Currently triggered from usb command but need to implement with no motion timer
2023-09-30 Will go to sleep if no movement seen for a period
2023-10-01 Added LED class to show state
2023-10-01 Started configuring gyro ready to EXT interrupt
2023-10-02 Start adding code to manage advertising timers without STM library
2023-10-03 Potentially fixed issue initialising RTC wake up interrupt
2023-10-03 Started cleaning up RTC code
2023-10-03 Fixed wake up from sleep using wrong clock
2023-10-03 Cleaned up sleep and low power modes
2023-10-04 Added flash configuration tool with options to save average offsets, timeouts etc
2023-10-04 Use Data Ready pin on Gyroscope to trigger read (rather than timer)
2023-10-04 Dynamically slow down gyroscope sampling rate if no movement detected
2023-10-05 Shutdown if battery falls below configurable level
2023-10-05 Moved Base LED handling to new class
2023-10-05 Cleaned up LED changes
2023-10-07 Base will periodically wake up remote to check battery level and flash if battery low
    Removed offsets from base as handled in remote
    Added config for battery warnings and sensitivity
2023-10-09 Reduced time before remote sleeps when no motion detected
2023-10-09 Starting to handle shutdown timeout when being woken remotely
2023-10-09 Preparing wake up test
2023-10-10 Inactivity timeout preserved even if woken for battery check
2023-10-10 Changing aci_gap_create_connection parameters to increase output rate
2023-10-12 Experiments with USB disabled current consumption; added invert to z axis
2023-10-12 Remote: only activate USB peripheral when powered
2023-10-12 More work trying to optimise sleep/shutdown
2023-10-12 Added option to choose between HSI and HSE in sleep mode
    HSI is more power efficient, but sometimes has problems waking up
2023-10-12 Reduced system clock from 64MHz to 32MHz
2023-10-13 Optimising sleep mechanism
2023-10-13 Enabled data and instruction cache in Base
    Clean up of HAL config file
2023-10-13 More STM files unused code removal
2023-10-13 Added schematic pdfs
